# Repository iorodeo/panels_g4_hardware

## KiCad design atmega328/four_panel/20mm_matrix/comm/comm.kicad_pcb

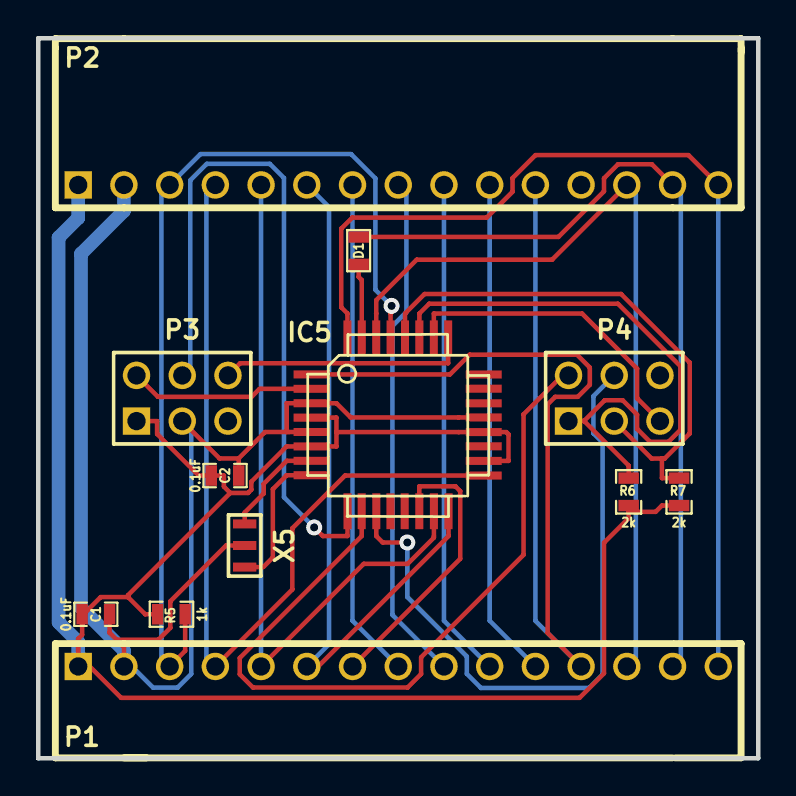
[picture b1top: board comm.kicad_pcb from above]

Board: 2 copper layers, 40.0 x 40.0 mm, 12 parts (0 on the bottom side), 26 nets.

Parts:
C1, C2: 0.1uF; SM0603_Capa
D1: DIODE; SM0603
IC5: ATMEGA328-A; TQFP32
P1: CONN15; HEADER_BOT
P2: CONN15; HEADER_TOP
P3, P4: CONN_3X2; pin_array_3x2
R5: 1k; SM0603_Resistor
R6, R7: 2k; SM0603_Resistor
X5: CER_RESO

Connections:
+5V: C1.1, C2.1, IC5.4, IC5.6, IC5.18, IC5.20, P1.1, P2.1, P3.1, R5.2, R6.1, R7.1
/CS1: IC5.14, P1.7
/CS2: P1.8, P2.7
/CS3: P1.9, P2.8
/CS4: P1.10, P2.9
/CS5: P1.11, P2.10
/CS6/EXT_INT1: IC5.1, P1.12, P2.11
/EXT_INT0: IC5.32, P1.15, P2.15
/MISO: IC5.16, P1.6, P2.6
/MOSI: IC5.15, P1.5, P2.5
/PCINT10/PC2: IC5.25, P3.6
/PCINT11/PC3: IC5.26, P4.5
/RESET_DRV1: IC5.2, P3.2
/RESET_DRV2: IC5.9, P3.4
/RESET_DRV3: IC5.10, P4.2
/RESET_DRV4: IC5.11, P4.4
/RESET_MSTR: IC5.29, P1.3, P2.3, R5.1
/RX: IC5.30, P1.13, P2.13
/SCK: IC5.17, P1.4, P2.4
/SCL: IC5.28, P4.3, R7.2
/SDA: IC5.27, P4.1, R6.2
/TX: D1.1, P1.14, P2.14
/XTAL1: IC5.7, X5.1
/XTAL2: IC5.8, X5.3
GND: C1.2, C2.2, IC5.3, IC5.5, IC5.21, P1.2, P2.2, P3.3, X5.2
unnamed: D1.2, IC5.31

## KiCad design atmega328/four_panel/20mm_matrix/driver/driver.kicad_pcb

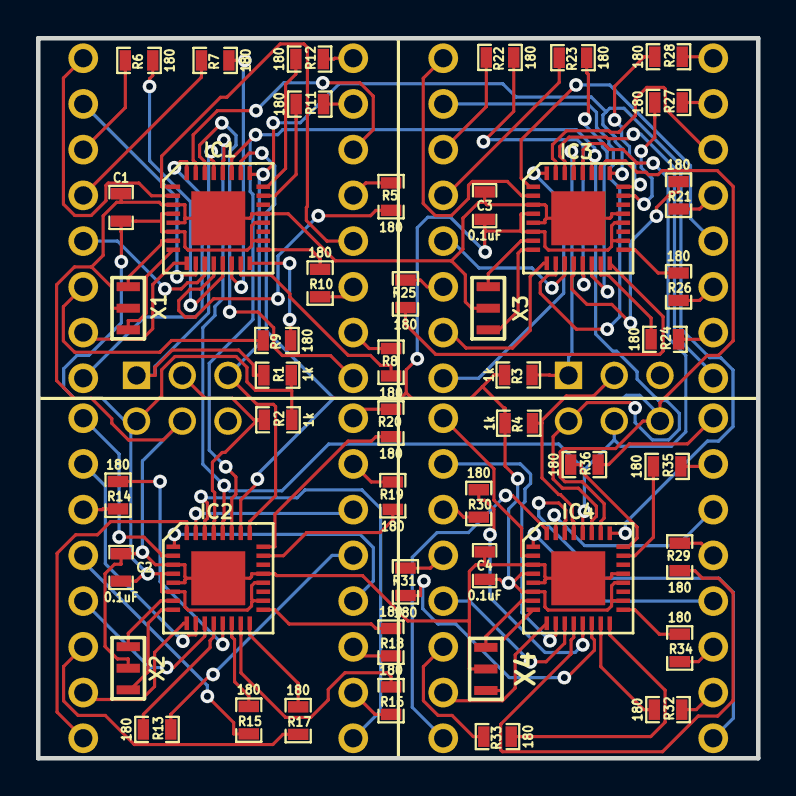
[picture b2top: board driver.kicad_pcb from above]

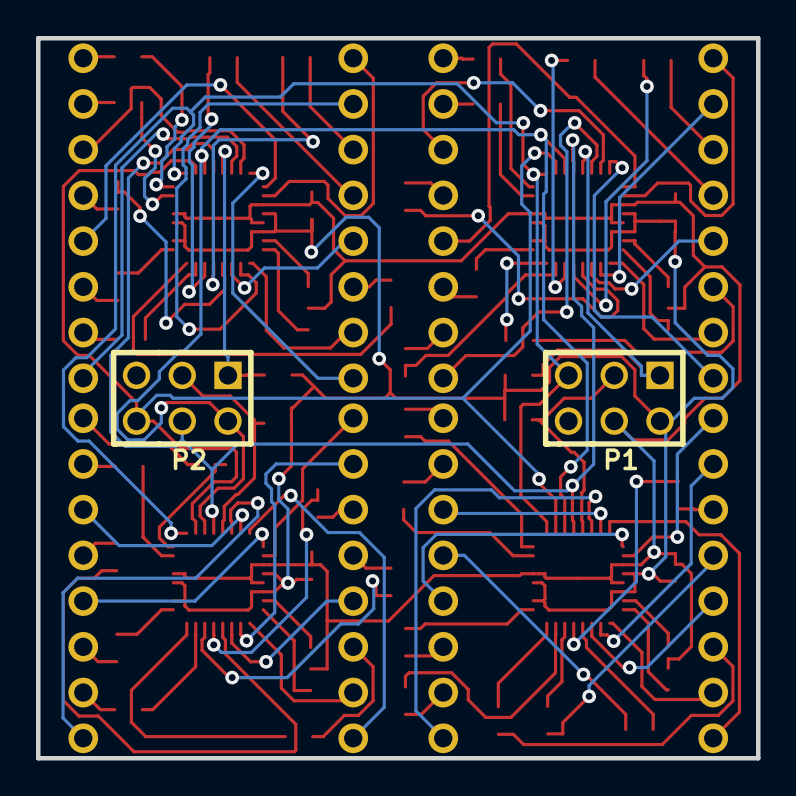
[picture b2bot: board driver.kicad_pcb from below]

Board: 2 copper layers, 40.0 x 40.0 mm, 54 parts (2 on the bottom side), 114 nets.

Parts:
C1, C2, C3, C4: 0.1uF; SM0603_Capa
IC1, IC2, IC3, IC4: ATMEGA328P-M; QFN32
MATRIX1, MATRIX2, MATRIX3, MATRIX4: LED_8X8; LED_MATRIX_20MM_8x8
P1, P2: CONN_3X2; PIN_ARRAY_F_3X2
R1, R2, R3, R4: 1k; SM0603_Resistor
R5, R6, R7, R8, R9, R10, R11, R12, R13, R14, R15, R16, R17, R18, R19, R20, R21, R22, R23, R24, R25, R26, R27, R28, R29, R30, R31, R32, R33, R34, R35, R36: 180; SM0603_Resistor
X1, X2, X3, X4: CER_RESO

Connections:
+5V: C1.1, C2.1, C3.1, C4.1, IC1.4, IC1.6, IC1.18, IC1.20, IC2.4, IC2.6, IC2.18, IC2.20, IC3.4, IC3.6, IC3.18, IC3.20, IC4.4, IC4.6, IC4.18, IC4.20, P1.1, R1.2, R2.2, R3.2, R4.2
/COL1_DRV1: IC1.30, MATRIX1.9
/COL1_DRV2: IC2.30, MATRIX2.9
/COL1_DRV3: IC3.30, MATRIX3.9
/COL1_DRV4: IC4.30, MATRIX4.9
/COL2_DRV1: IC1.31, MATRIX1.14
/COL2_DRV2: IC2.31, MATRIX2.14
/COL2_DRV3: IC3.31, MATRIX3.14
/COL2_DRV4: IC4.31, MATRIX4.14
/COL3_DRV1: IC1.32, MATRIX1.8
/COL3_DRV2: IC2.32, MATRIX2.8
/COL3_DRV3: IC3.32, MATRIX3.8
/COL3_DRV4: IC4.32, MATRIX4.8
/COL4_DRV1: IC1.1, MATRIX1.12
/COL4_DRV2: IC2.1, MATRIX2.12
/COL4_DRV3: IC3.1, MATRIX3.12
/COL4_DRV4: IC4.1, MATRIX4.12
/COL5_DRV1: IC1.2, MATRIX1.1
/COL5_DRV2: IC2.2, MATRIX2.1
/COL5_DRV3: IC3.2, MATRIX3.1
/COL5_DRV4: IC4.2, MATRIX4.1
/COL6_DRV1: IC1.9, MATRIX1.7
/COL6_DRV2: IC2.9, MATRIX2.7
/COL6_DRV3: IC3.9, MATRIX3.7
/COL6_DRV4: IC4.9, MATRIX4.7
/COL7_DRV1: IC1.10, MATRIX1.2
/COL7_DRV2: IC2.10, MATRIX2.2
/COL7_DRV3: IC3.10, MATRIX3.2
/COL7_DRV4: IC4.10, MATRIX4.2
/COL8_DRV1: IC1.11, MATRIX1.5
/COL8_DRV2: IC2.11, MATRIX2.5
/COL8_DRV3: IC3.11, MATRIX3.5
/COL8_DRV4: IC4.11, MATRIX4.5
/PCINT10/PC2: IC1.25, IC2.25, IC3.25, IC4.25, P1.6
/PCINT11/PC3: IC1.26, IC2.26, IC3.26, IC4.26, P2.5
/RESET_DRV1: IC1.29, P1.2, R1.1
/RESET_DRV2: IC2.29, P1.4, R2.1
/RESET_DRV3: IC3.29, P2.2, R3.1
/RESET_DRV4: IC4.29, P2.4, R4.1
/ROW1_DRV1: IC1.12, R5.1
/ROW1_DRV2: IC2.12, R13.1
/ROW1_DRV3: IC3.12, R21.1
/ROW1_DRV4: IC4.12, R29.1
/ROW2_DRV1: IC1.13, R6.1
/ROW2_DRV2: IC2.13, R14.1
/ROW2_DRV3: IC3.13, R22.1
/ROW2_DRV4: IC4.13, R30.1
/ROW3_DRV1: IC1.14, R7.1
/ROW3_DRV2: IC2.14, R15.1
/ROW3_DRV3: IC3.14, R23.1
/ROW3_DRV4: IC4.14, R31.1
/ROW4_DRV1: IC1.15, R8.1
/ROW4_DRV2: IC2.15, R16.1
/ROW4_DRV3: IC3.15, R24.1
/ROW4_DRV4: IC4.15, R32.1
/ROW5_DRV1: IC1.16, R9.1
/ROW5_DRV2: IC2.16, R17.1
/ROW5_DRV3: IC3.16, R25.1
/ROW5_DRV4: IC4.16, R33.1
/ROW6_DRV1: IC1.17, R10.1
/ROW6_DRV2: IC2.17, R18.1
/ROW6_DRV3: IC3.17, R26.1
/ROW6_DRV4: IC4.17, R34.1
/ROW7_DRV1: IC1.23, R11.1
/ROW7_DRV2: IC2.23, R19.1
/ROW7_DRV3: IC3.23, R27.1
/ROW7_DRV4: IC4.23, R35.1
/ROW8_DRV1: IC1.24, R12.1
/ROW8_DRV2: IC2.24, R20.1
/ROW8_DRV3: IC3.24, R28.1
/ROW8_DRV4: IC4.24, R36.1
/SCL: IC1.28, IC2.28, IC3.28, IC4.28, P2.3
/SDA: IC1.27, IC2.27, IC3.27, IC4.27, P2.1
/XTAL1_DRV1: IC1.7, X1.1
/XTAL1_DRV2: IC2.7, X2.1
/XTAL1_DRV3: IC3.7, X3.1
/XTAL1_DRV4: IC4.7, X4.1
/XTAL2_DRV1: IC1.8, X1.3
/XTAL2_DRV2: IC2.8, X2.3
/XTAL2_DRV3: IC3.8, X3.3
/XTAL2_DRV4: IC4.8, X4.3
GND: C1.2, C2.2, C3.2, C4.2, IC1.3, IC1.5, IC1.21, IC1.33, IC2.3, IC2.5, IC2.21, IC2.33, IC3.3, IC3.5, IC3.21, IC3.33, IC4.3, IC4.5, IC4.21, IC4.33, P1.3, X1.2, X2.2, X3.2, X4.2
unnamed: MATRIX3.11, R26.2
unnamed: MATRIX3.15, R27.2
unnamed: MATRIX3.16, R28.2
unnamed: MATRIX4.6, R33.2
unnamed: MATRIX4.11, R34.2
unnamed: MATRIX4.15, R35.2
unnamed: MATRIX4.16, R36.2
unnamed: MATRIX3.6, R25.2
unnamed: MATRIX4.3, R30.2
unnamed: MATRIX4.4, R31.2
unnamed: MATRIX4.13, R29.2
unnamed: MATRIX4.10, R32.2
unnamed: MATRIX3.3, R22.2
unnamed: MATRIX3.4, R23.2
unnamed: MATRIX3.13, R21.2
unnamed: MATRIX3.10, R24.2
unnamed: MATRIX1.3, R6.2
unnamed: MATRIX1.4, R7.2
unnamed: MATRIX1.13, R5.2
unnamed: MATRIX1.10, R8.2
unnamed: MATRIX2.13, R13.2
unnamed: MATRIX2.3, R14.2
unnamed: MATRIX2.4, R15.2
unnamed: MATRIX2.10, R16.2
unnamed: MATRIX2.6, R17.2
unnamed: MATRIX2.11, R18.2
unnamed: MATRIX2.15, R19.2
unnamed: MATRIX2.16, R20.2
unnamed: MATRIX1.6, R9.2
unnamed: MATRIX1.11, R10.2
unnamed: MATRIX1.15, R11.2
unnamed: MATRIX1.16, R12.2

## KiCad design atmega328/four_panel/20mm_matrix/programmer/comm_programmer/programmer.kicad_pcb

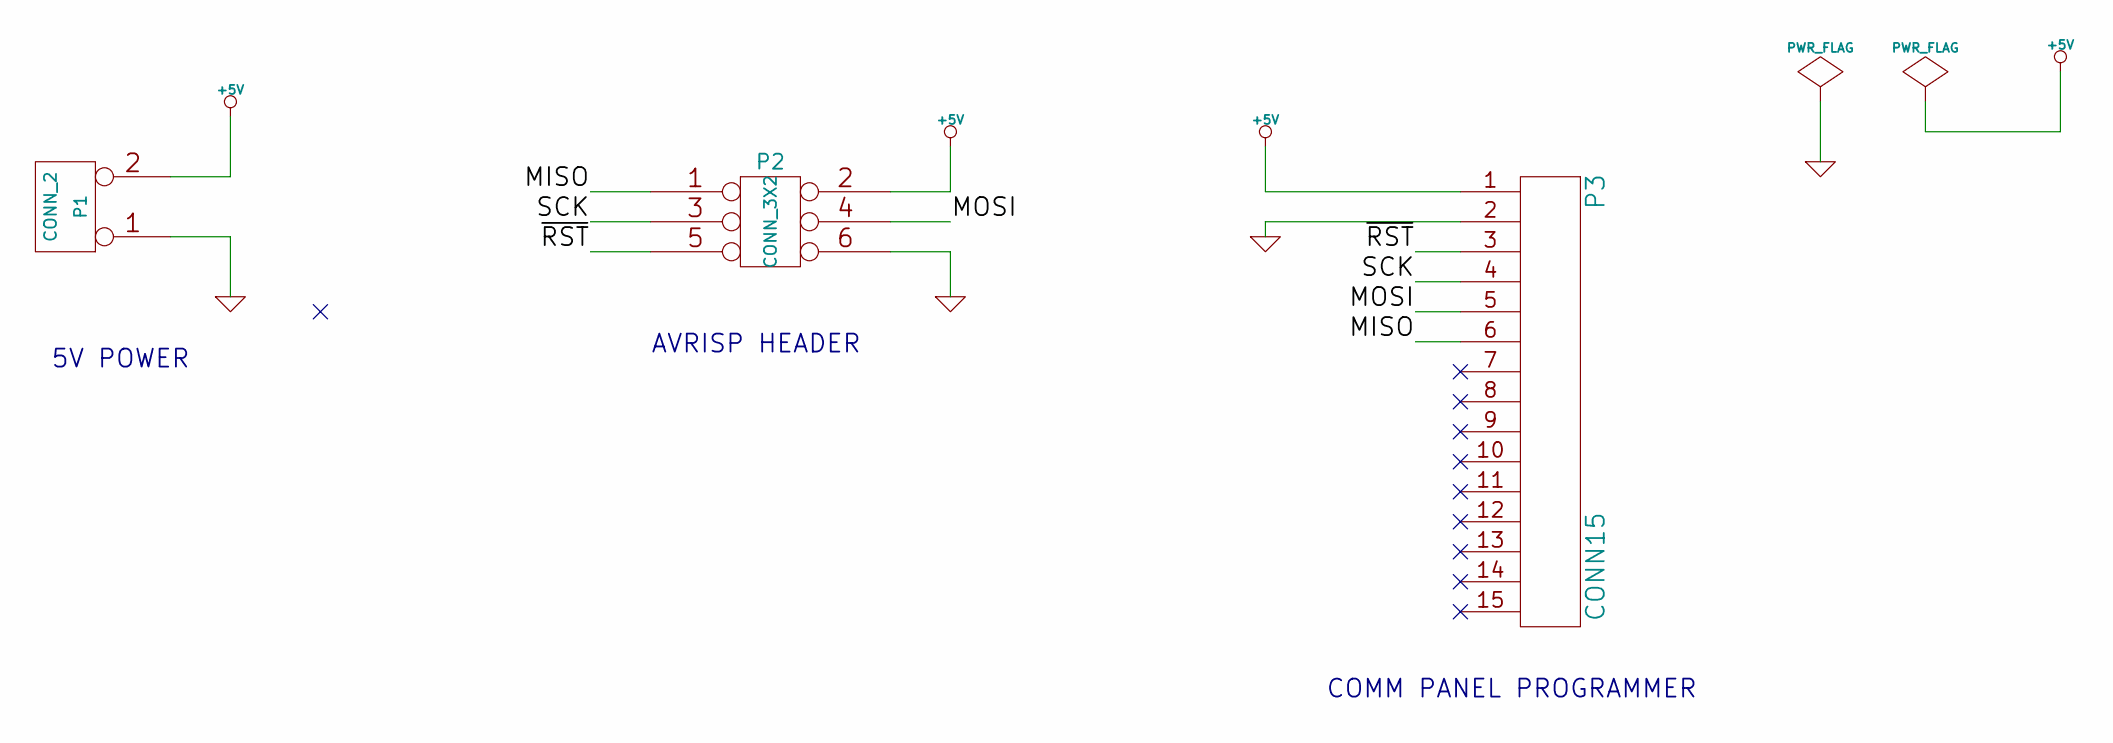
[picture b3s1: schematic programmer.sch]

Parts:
P1: CONN_2
P2: CONN_3X2
P3: CONN15

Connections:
+5V: P1.2 (PM), P2.2, P3.1
/MISO: P2.1, P3.6
/MOSI: P2.4, P3.5
/SCK: P2.3, P3.4
/~RST: P2.5, P3.3
GND: P1.1, P2.6, P3.2

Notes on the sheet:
AVRISP HEADER
5V POWER
COMM PANEL PROGRAMMER

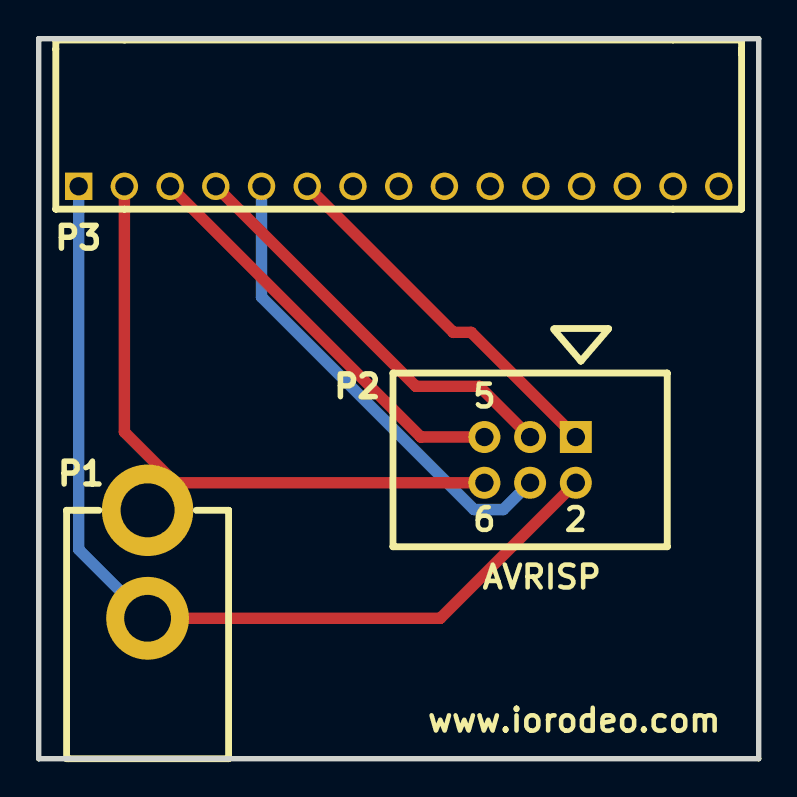
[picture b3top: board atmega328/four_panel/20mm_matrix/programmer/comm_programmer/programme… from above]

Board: 2 copper layers, 40.0 x 40.0 mm, 3 parts (0 on the bottom side), 6 nets.

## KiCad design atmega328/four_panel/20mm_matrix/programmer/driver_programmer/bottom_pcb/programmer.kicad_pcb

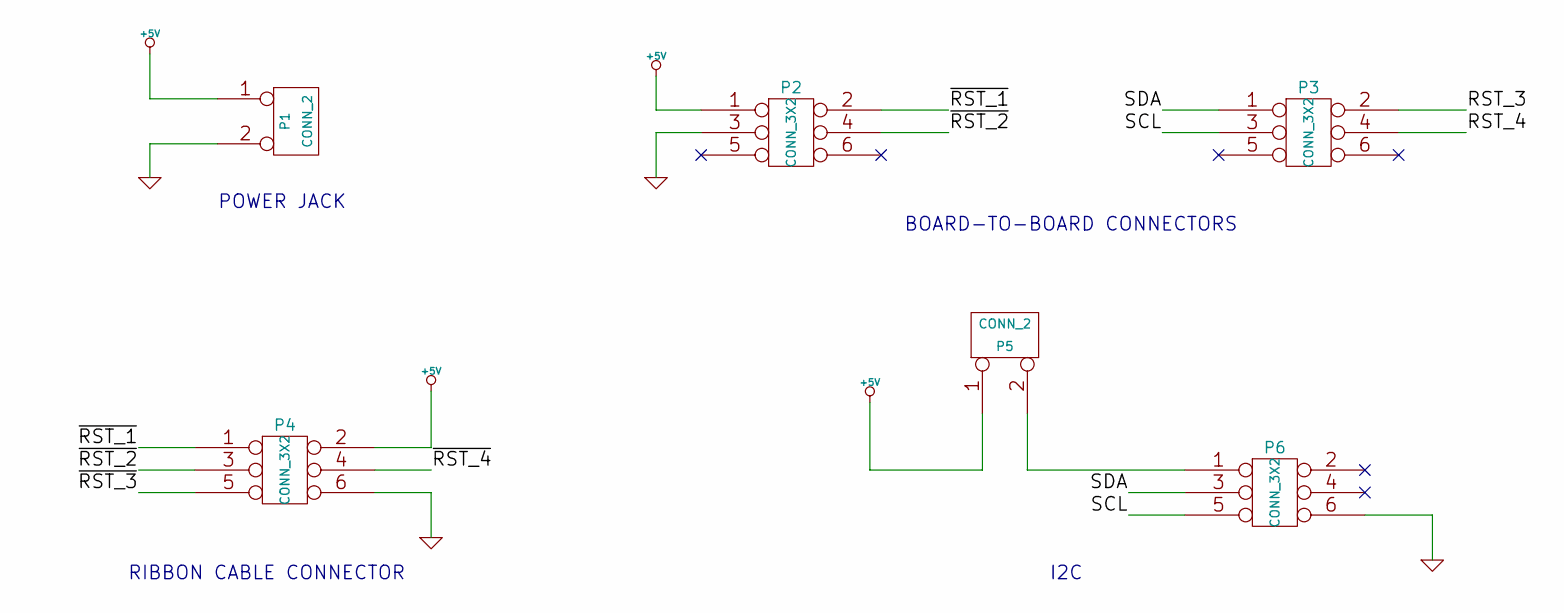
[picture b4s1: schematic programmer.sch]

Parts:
P1, P5: CONN_2
P2, P3, P4, P6: CONN_3X2

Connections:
+5V: P1.1, P2.1, P4.2, P5.1
/RST_3: P3.2
/RST_4: P3.4
/SCL: P3.3, P6.5
/SDA: P3.1, P6.3
/~RST_1: P2.2, P4.1
/~RST_2: P2.4, P4.3
/~RST_3: P4.5
/~RST_4: P4.4
GND: P1.2 (PM), P2.3, P4.6, P6.6
unnamed: P5.2 (PM), P6.1

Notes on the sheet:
POWER JACK
BOARD-TO-BOARD CONNECTORS
RIBBON CABLE CONNECTOR
I2C

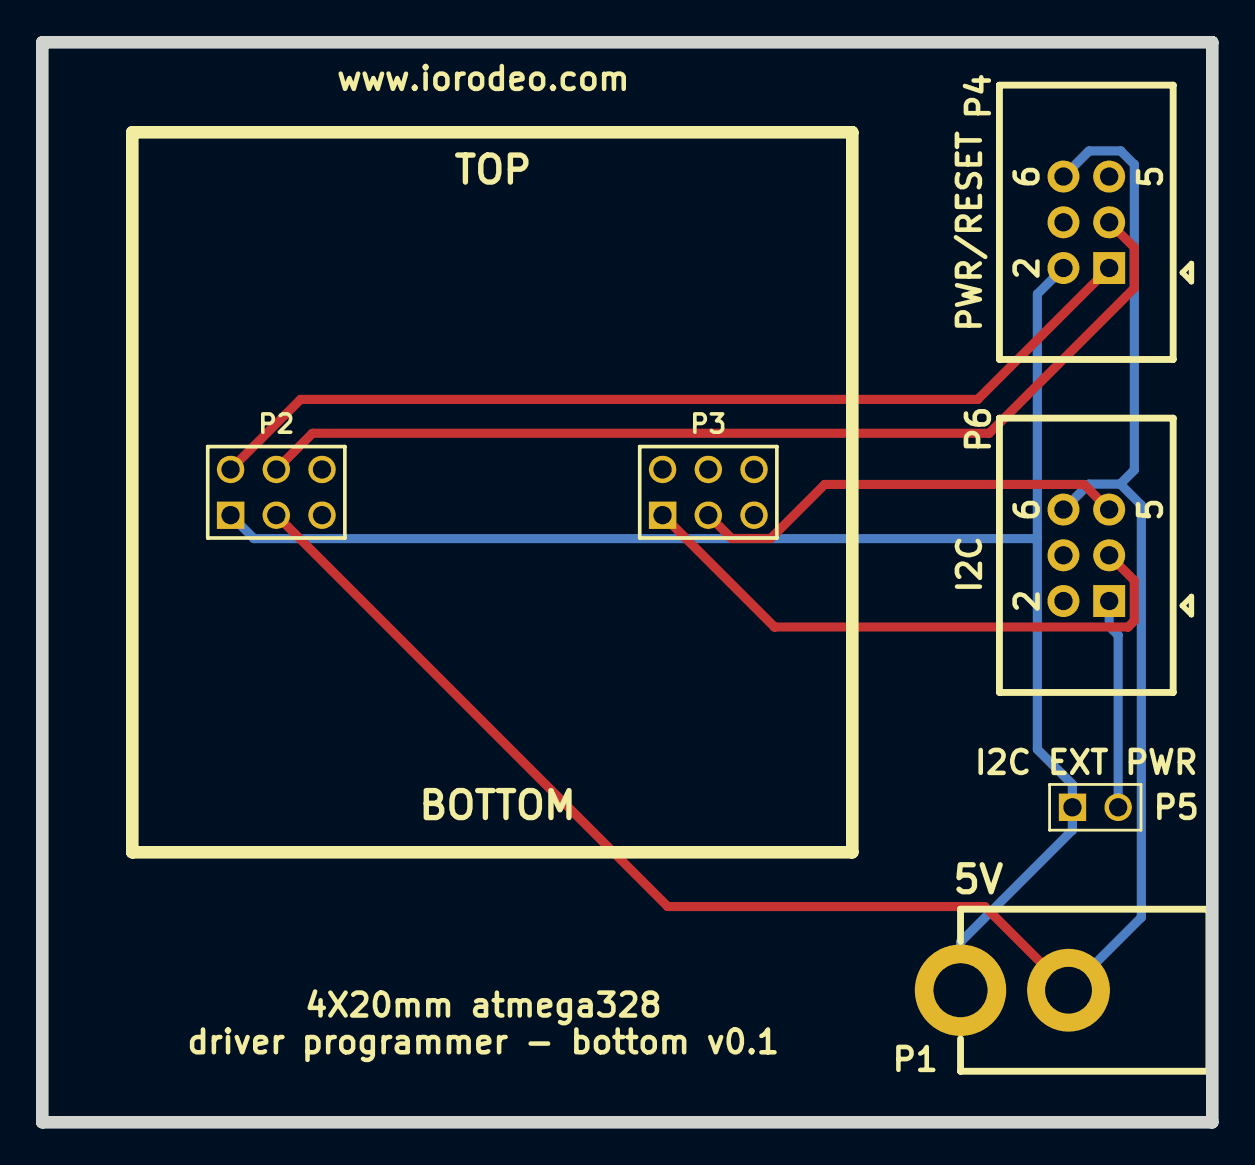
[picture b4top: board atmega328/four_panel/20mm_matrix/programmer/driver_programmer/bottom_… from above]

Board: 2 copper layers, 65.0 x 60.0 mm, 6 parts (0 on the bottom side), 7 nets.

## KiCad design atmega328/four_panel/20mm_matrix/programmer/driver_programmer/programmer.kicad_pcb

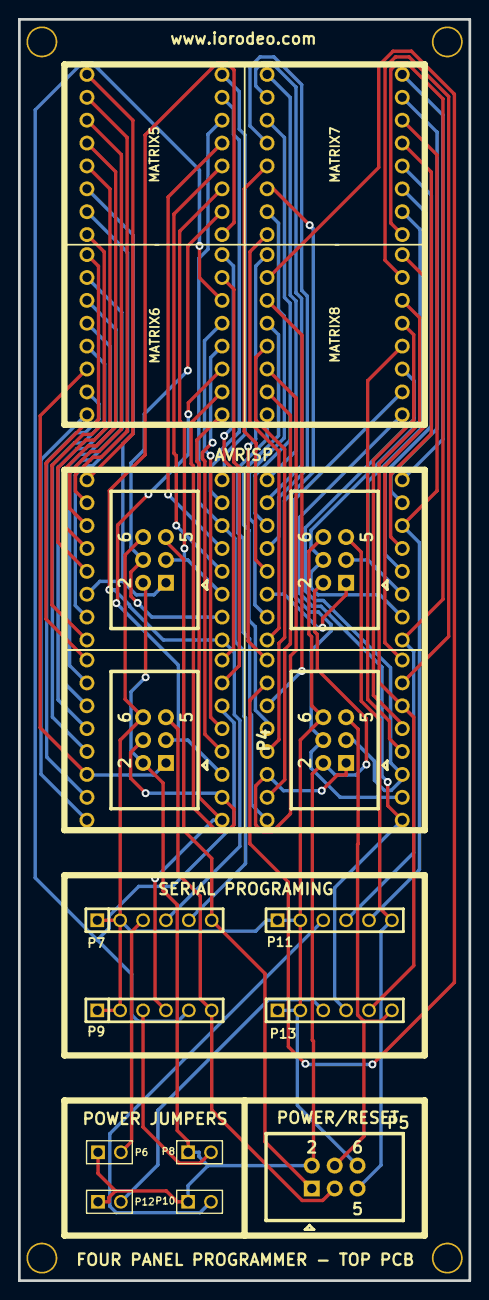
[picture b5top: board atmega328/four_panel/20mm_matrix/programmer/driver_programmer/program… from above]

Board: 2 copper layers, 50.0 x 140.0 mm, 25 parts (0 on the bottom side), 74 nets.

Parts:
4-40_1, 4-40_2, 4-40_3, 4-40_4: VAL**; 4-40
MATRIX1, MATRIX2, MATRIX3, MATRIX4, MATRIX5, MATRIX6, MATRIX7, MATRIX8: LED_8X8; LED_MATRIX_20MM_8x8
P1, P2, P3, P4, P5: CONN_3X2; 3X2_SHRD_HEADER
P6, P8, P10, P12: CONN_2; PIN_ARRAY_2X1
P7, P9, P11, P13: CONN_6; PIN_ARRAY-6X1

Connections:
+5V: P1.2, P2.2, P3.2, P4.2, P5.2, P6.1, P8.1, P10.1, P12.1
/A1_1: MATRIX1.13, MATRIX5.13
/A1_2: MATRIX2.13, MATRIX6.13
/A1_3: MATRIX3.13, MATRIX7.13
/A1_4: MATRIX4.13, MATRIX8.13
/A2_1: MATRIX1.3, MATRIX5.3
/A2_2: MATRIX2.3, MATRIX6.3
/A2_3: MATRIX3.3, MATRIX7.3
/A2_4: MATRIX4.3, MATRIX8.3
/A3_1: MATRIX1.4, MATRIX5.4
/A3_2: MATRIX2.4, MATRIX6.4
/A3_3: MATRIX3.4, MATRIX7.4
/A3_4: MATRIX4.4, MATRIX8.4
/A7_1: MATRIX1.15, MATRIX5.15
/A7_2: MATRIX2.15, MATRIX6.15
/A7_3: MATRIX3.15, MATRIX7.15
/A7_4: MATRIX4.15, MATRIX8.15
/A8_1: MATRIX1.16, MATRIX5.16
/A8_2: MATRIX2.16, MATRIX6.16
/A8_3: MATRIX3.16, MATRIX7.16
/A8_4: MATRIX4.16, MATRIX8.16
/C3_1: MATRIX1.8, MATRIX5.8
/C3_2: MATRIX2.8, MATRIX6.8
/C3_3: MATRIX3.8, MATRIX7.8
/C3_4: MATRIX4.8, MATRIX8.8
/C4_1: MATRIX1.12, MATRIX5.12
/C4_2: MATRIX2.12, MATRIX6.12
/C4_3: MATRIX3.12, MATRIX7.12
/C4_4: MATRIX4.12, MATRIX8.12
/C5_1: MATRIX1.1, MATRIX5.1
/C5_2: MATRIX2.1, MATRIX6.1
/C5_3: MATRIX3.1, MATRIX7.1
/C5_4: MATRIX4.1, MATRIX8.1
/C6_1: MATRIX1.7, MATRIX5.7
/C6_2: MATRIX2.7, MATRIX6.7
/C6_3: MATRIX3.7, MATRIX7.7
/C6_4: MATRIX4.7, MATRIX8.7
/C7_1: MATRIX1.2, MATRIX5.2
/C7_2: MATRIX2.2, MATRIX6.2
/C7_3: MATRIX3.2, MATRIX7.2
/C7_4: MATRIX4.2, MATRIX8.2
/C8_1: MATRIX1.5, MATRIX5.5
/C8_2: MATRIX2.5, MATRIX6.5
/C8_3: MATRIX3.5, MATRIX7.5
/C8_4: MATRIX4.5, MATRIX8.5
/MISO_1: MATRIX1.6, MATRIX5.6, P1.1
/MISO_2: MATRIX2.6, MATRIX6.6, P2.1
/MISO_3: MATRIX3.6, MATRIX7.6, P3.1
/MISO_4: MATRIX4.6, MATRIX8.6, P4.1
/MOSI_1: MATRIX1.10, MATRIX5.10, P1.4
/MOSI_2: MATRIX2.10, MATRIX6.10, P2.4
/MOSI_3: MATRIX3.10, MATRIX7.10, P3.4
/MOSI_4: MATRIX4.10, MATRIX8.10, P4.4
/RX_1: MATRIX1.9, MATRIX5.9, P7.4
/RX_2: MATRIX2.9, MATRIX6.9, P9.4
/RX_3: MATRIX3.9, MATRIX7.9, P11.4
/RX_4: MATRIX4.9, MATRIX8.9, P13.4
/SCK_1: MATRIX1.11, MATRIX5.11, P1.3
/SCK_2: MATRIX2.11, MATRIX6.11, P2.3
/SCK_3: MATRIX3.11, MATRIX7.11, P3.3
/SCK_4: MATRIX4.11, MATRIX8.11, P4.3
/TX_1: MATRIX1.14, MATRIX5.14, P7.5
/TX_2: MATRIX2.14, MATRIX6.14, P9.5
/TX_3: MATRIX3.14, MATRIX7.14, P11.5
/TX_4: MATRIX4.14, MATRIX8.14, P13.5
/~RST_1: P1.5, P5.1, P7.6
/~RST_2: P2.5, P5.3, P9.6
/~RST_3: P3.5, P5.5, P11.6
/~RST_4: P4.5, P5.4, P13.6
GND: P1.6, P2.6, P3.6, P4.6, P5.6, P7.1, P7.2, P9.1, P9.2, P11.1, P11.2, P13.1, P13.2
unnamed: P10.2, P11.3
unnamed: P8.2, P9.3
unnamed: P12.2, P13.3
unnamed: P6.2, P7.3

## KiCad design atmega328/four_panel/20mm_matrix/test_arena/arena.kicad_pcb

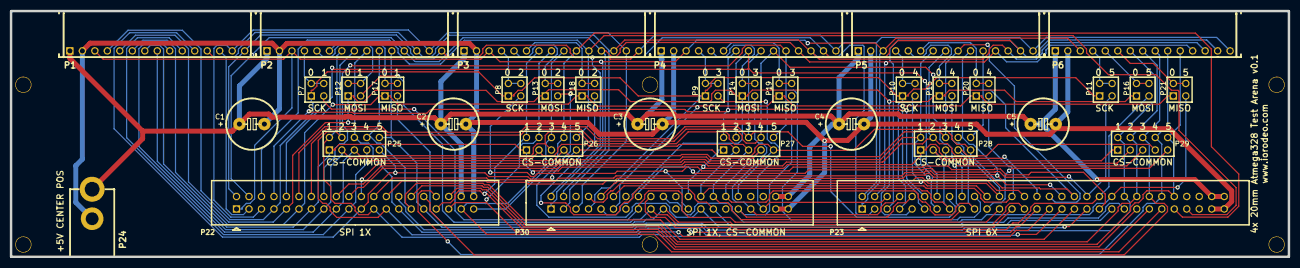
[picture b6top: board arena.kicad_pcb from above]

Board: 2 copper layers, 260.0 x 50.0 mm, 41 parts (0 on the bottom side), 70 nets.

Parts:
C1, C2, C3, C4, C5: 10uF; Capacitor_Polarized
M1, M2, M3, M4, M5, M6: VAL**; MOUNT_HOLE_4_40
P1, P2, P3, P4, P5, P6: CONN15; HEADER_TOP
P7, P8, P9, P10, P11, P12, P13, P14, P15, P16, P17, P18, P19, P20, P21: CONN_2X2; PIN_ARRAY_2X2
P22, P30: CONN_20X2; PIN_ARRAY_SHRD_20X2
P23: CONN_30X2; PIN_ARRAY_SHRD_30X2
P24: CONN_2; DCJACK_2PIN
P25, P26, P27, P28, P29: CONN_5X2; PIN_ARRAY_5x2

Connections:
+5V: C1.1, C2.1, C3.1, C4.1, C5.1, P1.1, P2.1, P3.1, P4.1, P5.1, P6.1, P22.38, P23.58, P23.60, P24.1, P30.38, P30.40
/CS1_0: P1.7, P22.13, P23.13, P25.1, P26.1, P27.1, P28.1, P29.1, P30.24
/CS1_1: P2.7, P22.23, P23.29, P25.2
/CS1_2: P3.7, P22.33, P23.45, P26.2
/CS1_3: P4.7, P22.8, P23.12, P27.2
/CS1_4: P5.7, P22.18, P23.28, P28.2
/CS1_5: P6.7, P22.28, P23.44, P29.2
/CS2_0: P1.8, P22.15, P23.15, P25.3, P26.3, P27.3, P28.3, P29.3, P30.26
/CS2_1: P2.8, P22.25, P23.31, P25.4
/CS2_2: P3.8, P22.35, P23.47, P26.4
/CS2_3: P4.8, P22.10, P23.14, P27.4
/CS2_4: P5.8, P22.20, P23.30, P28.4
/CS2_5: P6.8, P22.30, P23.46, P29.4
/CS3_0: P1.9, P22.17, P23.17, P25.5, P26.5, P27.5, P28.5, P29.5, P30.28
/CS3_1: P2.9, P22.27, P23.33, P25.6
/CS3_2: P3.9, P22.37, P23.49, P26.6
/CS3_3: P4.9, P22.12, P23.16, P27.6
/CS3_4: P5.9, P22.22, P23.32, P28.6
/CS3_5: P6.9, P22.32, P23.48, P29.6
/CS4_0: P1.10, P22.19, P23.19, P25.7, P26.7, P27.7, P28.7, P29.7, P30.30
/CS4_1: P2.10, P22.29, P23.35, P25.8
/CS4_2: P3.10, P22.39, P23.51, P26.8
/CS4_3: P4.10, P22.14, P23.18, P27.8
/CS4_4: P5.10, P22.24, P23.34, P28.8
/CS4_5: P6.10, P22.34, P23.50, P29.8
/CS5_0: P1.11, P22.21, P23.21, P25.9, P26.9, P27.9, P28.9, P29.9, P30.32
/CS5_1: P2.11, P22.31, P23.37, P25.10
/CS5_2: P3.11, P22.6, P23.53, P26.10
/CS5_3: P4.11, P22.16, P23.20, P27.10
/CS5_4: P5.11, P22.26, P23.36, P28.10
/CS5_5: P6.11, P22.36, P23.52, P29.10
/EXT_INT0: P1.15, P2.15, P3.15, P4.15, P5.15, P6.15, P22.2, P23.2, P30.2
/EXT_INT1: P1.12, P2.12, P3.12, P4.12, P5.12, P6.12, P22.4, P23.4, P30.4
/MISO_0: P1.6, P17.1, P18.1, P19.1, P20.1, P21.1, P22.11, P23.11, P30.11
/MISO_1: P17.3, P23.27, P30.19
/MISO_2: P18.3, P23.43, P30.27
/MISO_3: P19.3, P23.10, P30.31
/MISO_4: P20.3, P23.26, P30.12
/MISO_5: P21.3, P23.42, P30.20
/MISO_11: P2.6, P17.2, P17.4
/MISO_22: P3.6, P18.2, P18.4
/MISO_33: P4.6, P19.2, P19.4
/MISO_44: P5.6, P20.2, P20.4
/MISO_55: P6.6, P21.2, P21.4
/MOSI_0: P1.5, P12.1, P13.1, P14.1, P15.1, P16.1, P22.9, P23.9, P30.9
/MOSI_1: P12.3, P23.25, P30.17
/MOSI_2: P13.3, P23.41, P30.25
/MOSI_3: P14.3, P23.8, P30.33
/MOSI_4: P15.3, P23.24, P30.10
/MOSI_5: P16.3, P23.40, P30.18
/MOSI_11: P2.5, P12.2, P12.4
/MOSI_22: P3.5, P13.2, P13.4
/MOSI_33: P4.5, P14.2, P14.4
/MOSI_44: P5.5, P15.2, P15.4
/MOSI_55: P6.5, P16.2, P16.4
/RESET_MSTR: P1.3, P2.3, P3.3, P4.3, P5.3, P6.3, P22.1, P23.1, P30.1
/RX: P1.13, P2.13, P3.13, P4.13, P5.13, P6.13, P22.3, P23.3, P30.3
/SCK_0: P1.4, P7.1, P8.1, P9.1, P10.1, P11.1, P22.7, P23.7, P30.7
/SCK_1: P7.3, P23.23, P30.15
/SCK_2: P8.3, P23.39, P30.23
/SCK_3: P9.3, P23.6, P30.35
/SCK_4: P10.3, P23.22, P30.8
/SCK_5: P11.3, P23.38, P30.16
/SCK_11: P2.4, P7.2, P7.4
/SCK_22: P3.4, P8.2, P8.4
/SCK_33: P4.4, P9.2, P9.4
/SCK_44: P5.4, P10.2, P10.4
/SCK_55: P6.4, P11.2, P11.4
/TX: P1.14, P2.14, P3.14, P4.14, P5.14, P6.14, P22.5, P23.5, P30.5
GND: C1.2, C2.2, C3.2, C4.2, C5.2, P1.2, P2.2, P3.2, P4.2, P5.2, P6.2, P22.40, P23.57, P23.59, P24.2, P30.37, P30.39
